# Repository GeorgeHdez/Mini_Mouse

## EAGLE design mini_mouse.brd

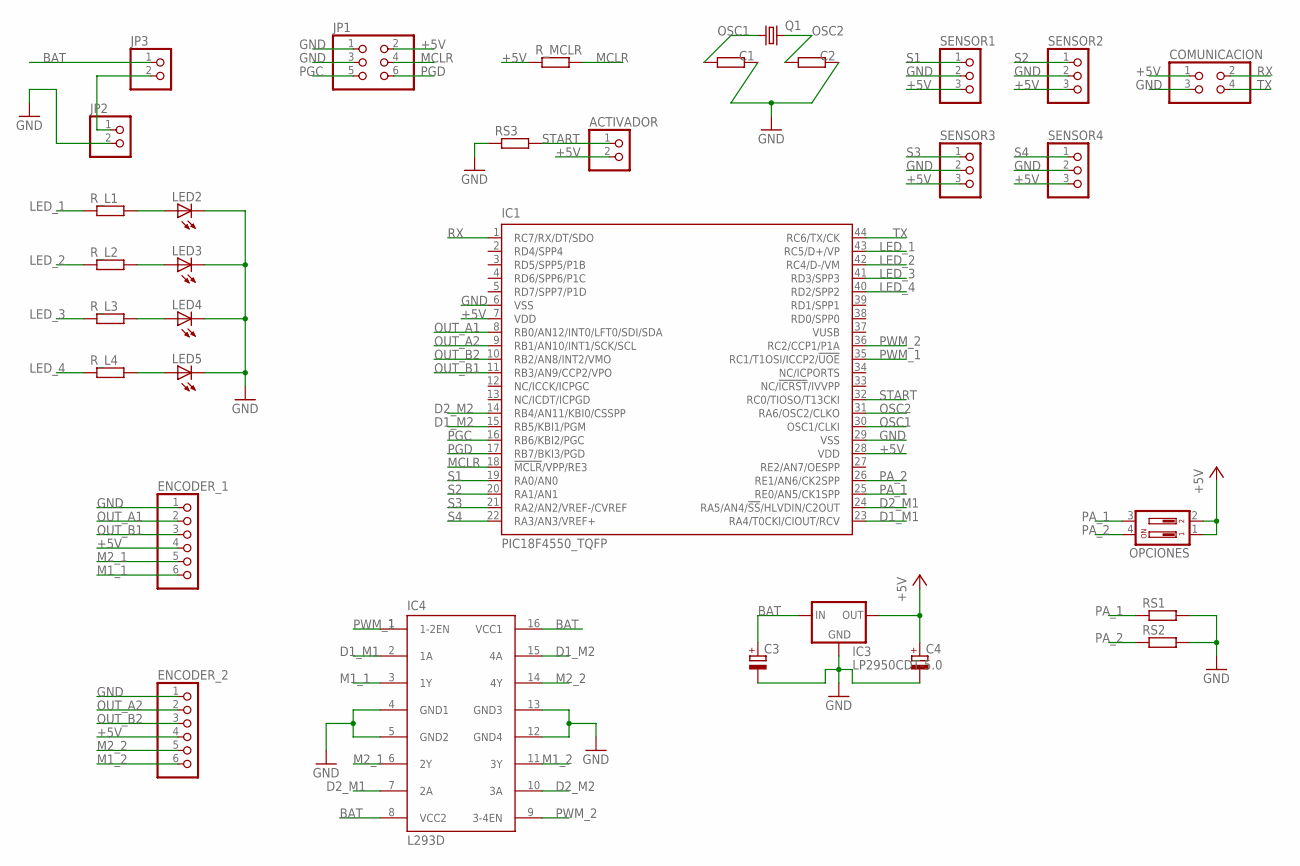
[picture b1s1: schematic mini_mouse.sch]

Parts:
ACTIVADOR: PINHD-1X2; 1X02
C1, C2: R-EU_R0805; R0805
C3, C4: CPOL-EUE2-4; E2-4
COMUNICACION: PINHD-2X2; 2X02
ENCODER_1, ENCODER_2: PINHD-1X6; 1X06
IC1: PIC18F4550_TQFP; TQFP44
IC3: LP2950CDT-5.0; DPACK
IC4: L293D; DIL16
JP1: PINHD-2X3; 2X03
JP2, JP3: PINHD-1X2; 1X02
LED2, LED3, LED4, LED5: LED3MM
OPCIONES: DIP02YL
Q1: CRYSTALHC49U-V; HC49U-V
RS1, RS2, RS3: R-EU_R0805; R0805
R_L1, R_L2, R_L3, R_L4: R-EU_R0805; R0805
R_MCLR: R-EU_R0805; R0805
SENSOR1, SENSOR2, SENSOR3, SENSOR4: PINHD-1X3; 1X03

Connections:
+5V: ACTIVADOR.2, C4.+, COMUNICACION.1, ENCODER_1.4, ENCODER_2.4, IC1.7 (VDD), IC1.28 (VDD), IC3.3 (OUT), JP1.2, OPCIONES.1, OPCIONES.2, R_MCLR.1, SENSOR1.3, SENSOR2.3, SENSOR3.3, SENSOR4.3
BAT: C3.+, IC3.1 (IN), IC4.8 (VCC2), IC4.16 (VCC1), JP3.1
D1_M1: IC1.23 (RA4/T0CKI/CIOUT/RCV), IC4.2 (1A)
D1_M2: IC1.15 (RB5/KBI1/PGM), IC4.15 (4A)
D2_M1: IC1.24 (RA5/AN4/!SS!/HLVDIN/C2OUT), IC4.7 (2A)
D2_M2: IC1.14 (RB4/AN11/KBI0/CSSPP), IC4.10 (3A)
GND: C1.2, C2.2, C3.-, C4.-, COMUNICACION.3, ENCODER_1.1, ENCODER_2.1, IC1.6 (VSS), IC1.29 (VSS), IC3.4 (GND), IC4.4 (GND1), IC4.5 (GND2), IC4.12 (GND4), IC4.13 (GND3), JP1.1, JP1.3, JP2.2, LED2.K (C), LED3.K (C), LED4.K (C), LED5.K (C), RS1.2, RS2.2, RS3.1, SENSOR1.2, SENSOR2.2, SENSOR3.2, SENSOR4.2
LED_1: IC1.43 (RC5/D+/VP), R_L1.1
LED_2: IC1.42 (RC4/D-/VM), R_L2.1
LED_3: IC1.41 (RD3/SPP3), R_L3.1
LED_4: IC1.40 (RD2/SPP2), R_L4.1
M1_1: ENCODER_1.6, IC4.3 (1Y)
M1_2: ENCODER_2.6, IC4.11 (3Y)
M2_1: ENCODER_1.5, IC4.6 (2Y)
M2_2: ENCODER_2.5, IC4.14 (4Y)
MCLR: IC1.18 (!MCLR!/VPP/RE3), JP1.4, R_MCLR.2
unnamed: LED2.A, R_L1.2
unnamed: LED3.A, R_L2.2
unnamed: LED4.A, R_L3.2
unnamed: LED5.A, R_L4.2
unnamed: JP2.1, JP3.2
OSC1: C1.1, IC1.30 (OSC1/CLKI), Q1.1
OSC2: C2.1, IC1.31 (RA6/OSC2/CLKO), Q1.2
OUT_A1: ENCODER_1.2, IC1.8 (RB0/AN12/INT0/LFT0/SDI/SDA)
OUT_A2: ENCODER_2.2, IC1.9 (RB1/AN10/INT1/SCK/SCL)
OUT_B1: ENCODER_1.3, IC1.11 (RB3/AN9/CCP2/VPO)
OUT_B2: ENCODER_2.3, IC1.10 (RB2/AN8/INT2/VMO)
PA_1: IC1.25 (RE0/AN5/CK1SPP), OPCIONES.3, RS1.1
PA_2: IC1.26 (RE1/AN6/CK2SPP), OPCIONES.4, RS2.1
PGC: IC1.16 (RB6/KBI2/PGC), JP1.5
PGD: IC1.17 (RB7/BKI3/PGD), JP1.6
PWM_1: IC1.35 (RC1/T1OSI/ICCP2/!UOE), IC4.1 (1-2EN)
PWM_2: IC1.36 (RC2/CCP1/P1A), IC4.9 (3-4EN)
RX: COMUNICACION.2, IC1.1 (RC7/RX/DT/SDO)
S1: IC1.19 (RA0/AN0), SENSOR1.1
S2: IC1.20 (RA1/AN1), SENSOR2.1
S3: IC1.21 (RA2/AN2/VREF-/CVREF), SENSOR3.1
S4: IC1.22 (RA3/AN3/VREF+), SENSOR4.1
START: ACTIVADOR.1, IC1.32 (RC0/TIOSO/T13CKI), RS3.2
TX: COMUNICACION.4, IC1.44 (RC6/TX/CK)

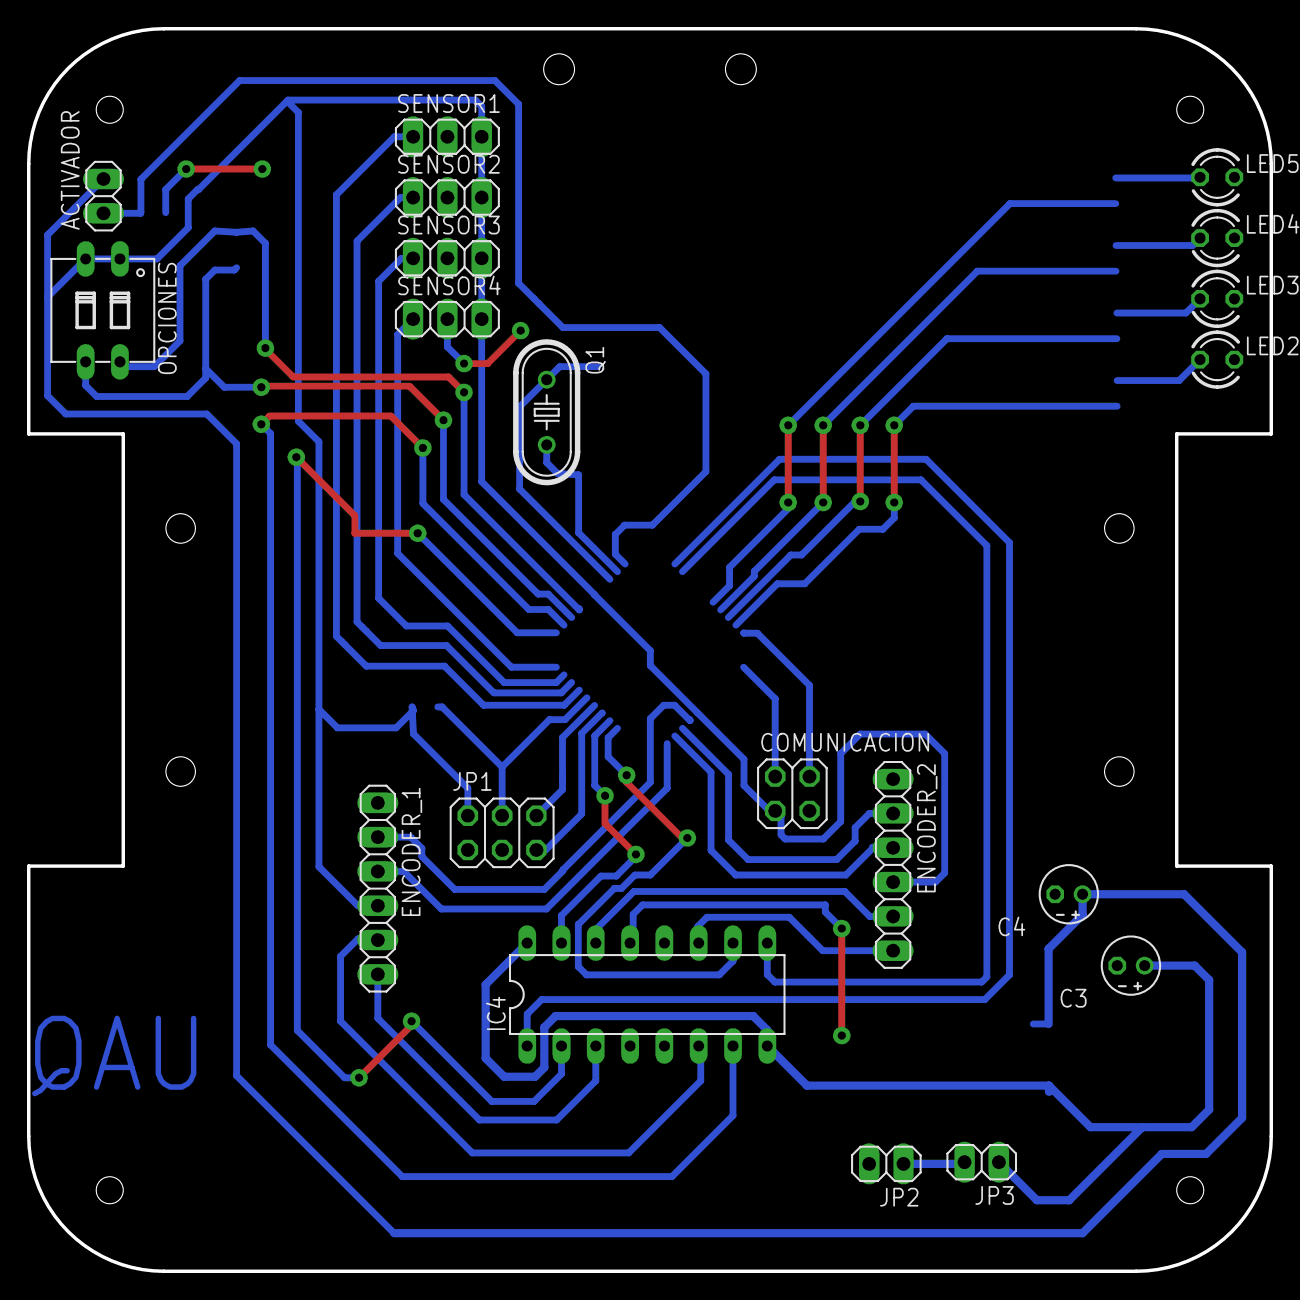
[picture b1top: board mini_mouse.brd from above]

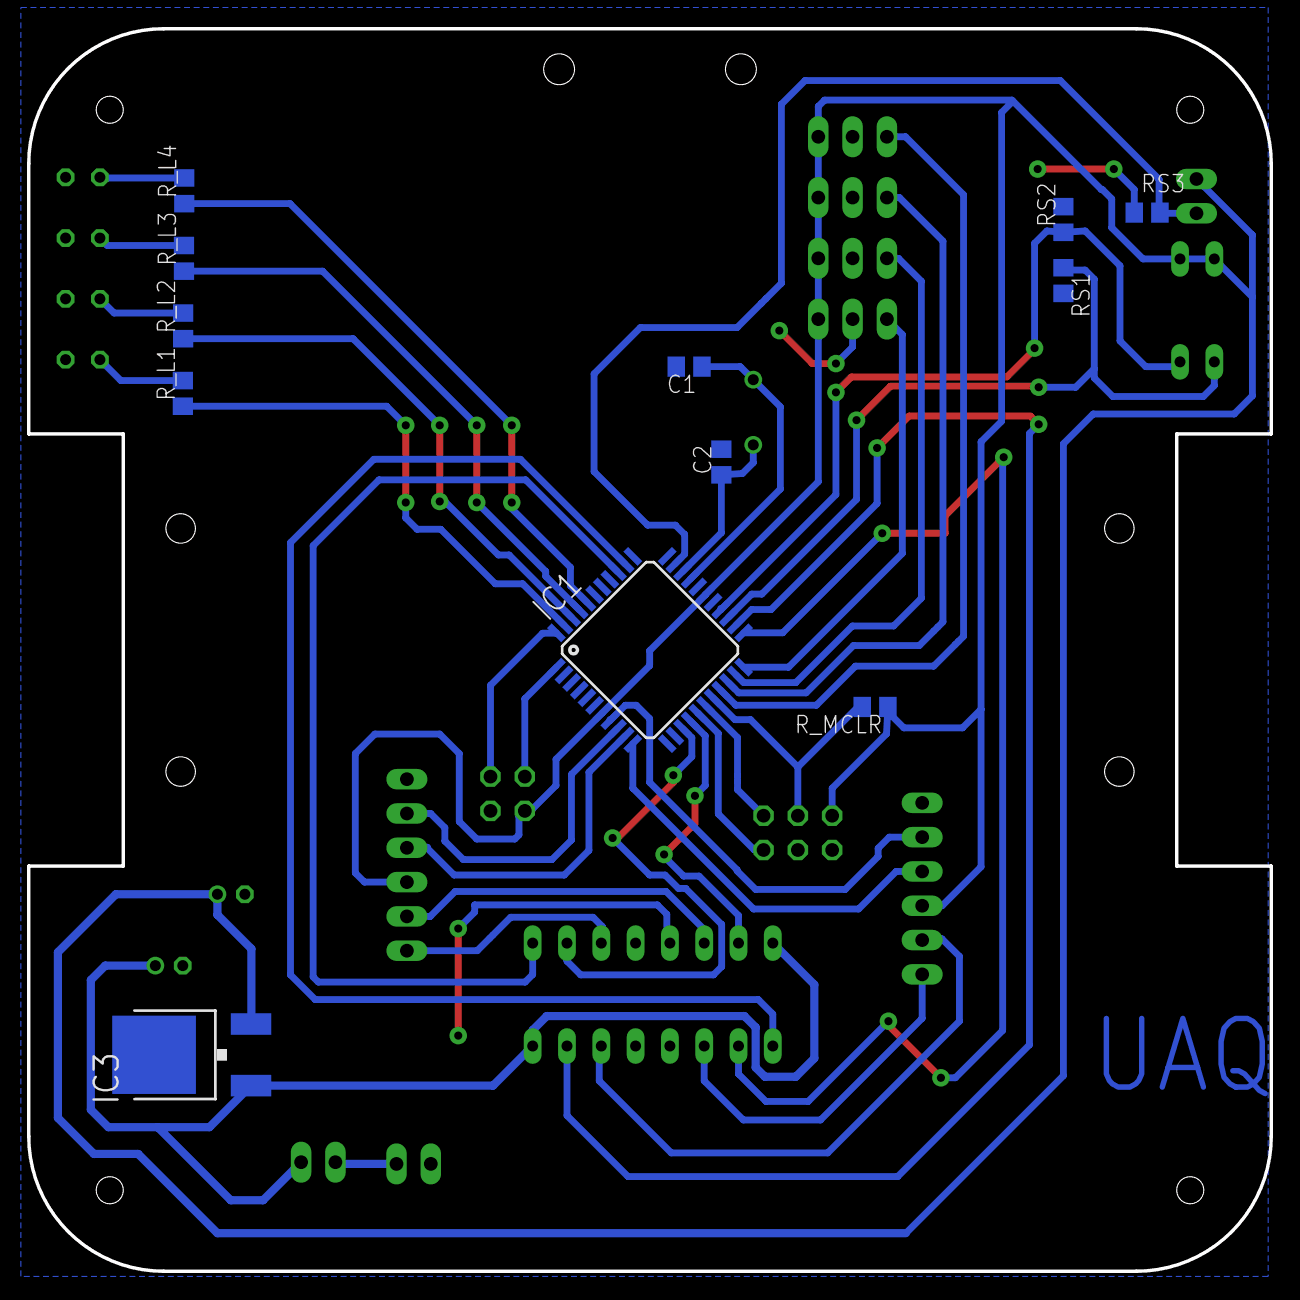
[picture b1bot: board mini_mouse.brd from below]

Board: 2 copper layers, 92.0 x 92.0 mm, 32 parts (12 on the bottom side), 40 nets.

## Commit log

2019-04-20 initial commit
    start project
2019-04-20 Avance
    Pines para direccion
    Pines PWM
    Leds
    Reset
    Programador
    Oscilador
2019-04-20 Reacomodo
    Se acomodaron los componentes del esquematico
2019-04-20 Componentes agregados
    Encoder, puente h, switches, clemas alimentacion
2019-04-20 Regulador
    Se agregò el regulador de voltaje
2019-04-20 Create a board file
    Se creo el archivo para la tarjeta
2019-04-20 initialize develope mechanic designe
2019-04-21 Diseño Basico
    Dimencionamiento del contorno del robot
2019-04-21 Agregar regulador de voltaje
    Se modificó el archivo para agregar un regulador de voltaje a 5V
2019-04-22 Cambios en componentes
    Se cambiaron los empaquetados de algunos componentes como regulador de voltaje junto con sus capacitores. Se agregaron botones para las secuencias y on/off
2019-04-22 Cambios finales a esquemático, inicio de board
    Se realizaron los ultimos cambios al esquemático. Se empezó el diseño del pcb
2019-04-23 pcb
    Se realizò PCB en un 90%
2019-04-23 Ajuste PCB
    Se realizó el ajuste del pcb
2019-04-23 Soporte Exterior
    Se creo el soporte exterior
2019-04-24 Pads correctos
    Se agregaron los pads deseados y se terminaron de cablear componentes faltantes
2019-04-24 Cambiar tamaño de las llantas
    Se cambio el ancho de las llantas para que coincidiera con las nuevas de 32mm de diametro
2019-04-24 Acomodo de leds
    Se centraron los leds
2019-04-24 Reacomodo de Vias
    Se reacomodaron componentes por conflictos con diseño mecanico
2019-04-24 Simplificar Documento
    Se borraron documentos incecesarios
2019-04-25 Cambio de dimensiones de tarjeta
    Se cambio las distancia que ocupan las ruedas de 32 mm de diametro
2019-04-25 Acomodo de pines comunicación y puentes
    Se acomodaron los puentes y se cambió el conector para el módulo Bluetooth
2019-04-25 Cambios en puentes
    Se hicieron modificaciones en los puentes para una mejor limpieza en la placa
2019-04-25 Agregar componentes
    Se agregaron los componentes de motores, brakets y llantas para verificar el estado del dispositivo
2019-04-25 Leds re-acomodados
    Se acomodaron los LEDS del lado derecho de la placa.
2019-04-25 Actualizar Drill
    Actualizacion de los drilles para la rueda loca
2019-04-25 Acomodo de la rueda loca
    Nuevo diseño de la PCB
2019-04-25 Actualización Board
    Se actualizo la distribucion de componentes, se cambio el tamaño de los package de las resistencias y capacitores smd y se modifico la forma de la tarjeta.
2019-05-12 Final Designe
2019-05-15 Mechanic FInal
